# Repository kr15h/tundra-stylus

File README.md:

# Tundra Stylus

> This project has migrated. See [Lighthouse Stylus](https://gitlab.com/kriwkrow/lighthouse-stylus).

Tundra Tracker stylus baseplate for 3D positional tracking. This repository contains design files and test application source code. It currently works with [SteamVR](https://store.steampowered.com/app/250820/SteamVR/), but [libsurvive](https://github.com/cntools/libsurvive) support is on its way.

https://github.com/user-attachments/assets/fd64adfa-e3c0-4b6a-a956-ca7f262a2909

## Introduction

Vive Lighthouse system is great! The main use of it is VR, but what about drawing or painting in space? Stylus input is the natural choice of many, but there is no VIVE Lighthouse Stylus available. Logitech almost launched VR Ink, but then decided not to. What to do?

[Tundra Tracker](https://tundra-labs.com/products/additional-tracker) is the smallest available off-the-shelve tracker that is compatible with the VIVE Lighthouse system. It offers a great deal of flexibility via its [IO Expansion Board](https://tundra-labs.com/products/tundra-tracker-io-expansion-board). With that in mind, all we need is a neat circuit board with buttons and a 3D-printable structure that looks and feels like a stylus. 

And that is Tundra Stylus! Produce the circuit board, 3D print the enclosure and you are ready to go, given that you have the Tundra Tracker and its IO Expansion board.

## Getting Started

Here is a table of contents of different documentation sections that will tell you what to do. You can also jump right to the design, electronics and software sections if you know all that by heart and prefer not to read too much documentation. It is up to you.

- [BOM](docs/BOM.md)  
  Start here as you will need to purchase some things to get started.
- [PCB Production](docs/PCB_PRODUCTION.md)  
  This may take time too so better start early.
- [3D Printing](docs/3D_PRINTING.md)  
  This one is relatively fast, given you have FDM printer available.
- [Assembly](docs/ASSEMBLY.md)  
  Putting it all together should be not hard, given you have all the parts (and tools).
- [Usage](docs/USAGE.md)  
  The setup and software part of the process.
- [Contributing](docs/CONTRIBUTING.md)  
  You are willing to improve something? Great!

## License

This repository contains multiple components, each licensed under different terms. Please review the specific license for each component below.

1. The CAD files in this repository are licensed under the **Creative Commons Attribution-NonCommercial 4.0 International (CC BY-NC 4.0)**.
2. The electronics design files in this repository are licensed under the **Creative Commons Attribution-NonCommercial 4.0 International (CC BY-NC 4.0)**.
3. The source code in this repository is licensed under the **MIT License**.

Please consult [LICENSE.md](LICENSE.md) for more detail.

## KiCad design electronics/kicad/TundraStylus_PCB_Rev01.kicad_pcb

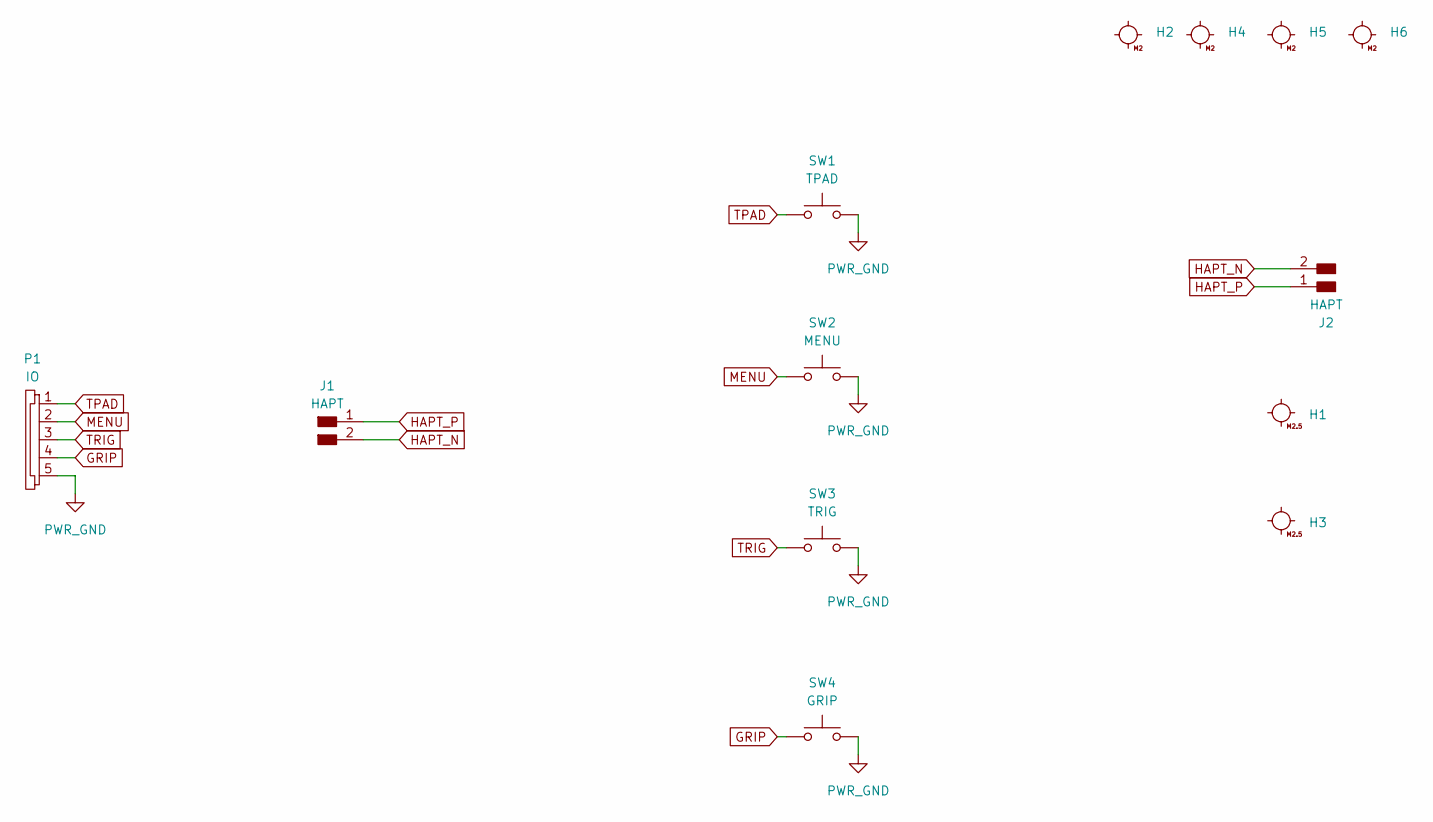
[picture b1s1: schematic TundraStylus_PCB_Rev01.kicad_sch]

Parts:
H1, H3: MountingHole_M2.5
H2, H4, H5, H6: MountingHole_M2
J1, J2: HAPT; Conn_2pos_Plain
P1: IO; Conn_FFC_1x05_P1mm_SideEntry_GCT_FFC3B11-05-T
SW1: TPAD; Button_Omron_B3SN_6.0x6.0mm
SW2: MENU; Button_Omron_B3SN_6.0x6.0mm
SW3: TRIG; Button_Omron_B3SN_6.0x6.0mm
SW4: GRIP; Button_Omron_B3SN_6.0x6.0mm

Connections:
GRIP: P1.4, SW4.1
HAPT_N: J1.2, J2.2
HAPT_P: J1.1, J2.1
MENU: P1.2, SW2.1
PWR_GND: P1.5, SW1.2, SW2.2, SW3.2, SW4.2
TPAD: P1.1, SW1.1
TRIG: P1.3, SW3.1

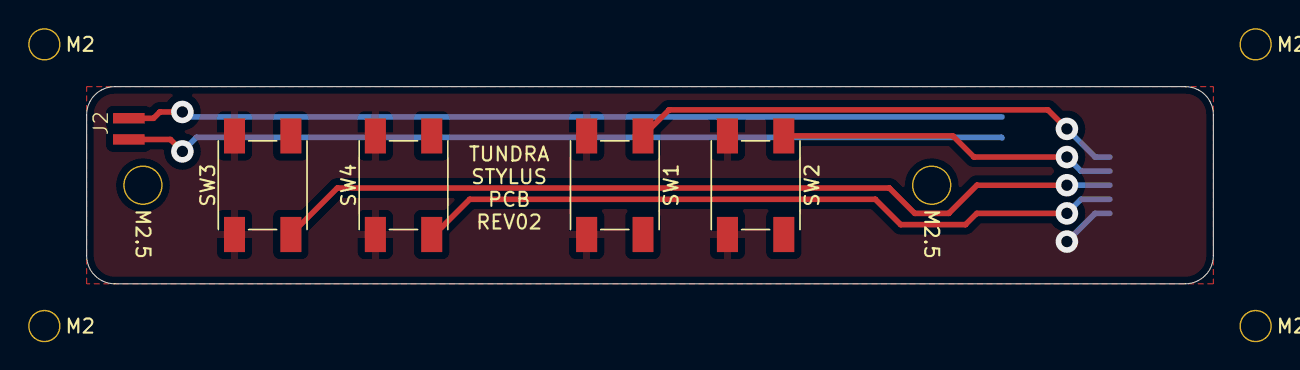
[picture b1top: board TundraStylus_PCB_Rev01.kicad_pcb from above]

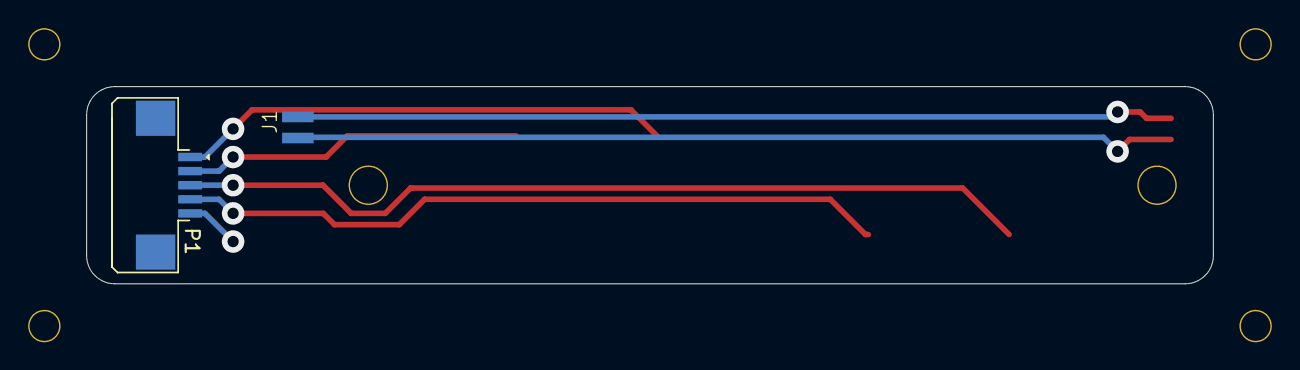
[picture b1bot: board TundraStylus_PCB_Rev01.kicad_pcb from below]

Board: 2 copper layers, 80.0 x 14.0 mm, 13 parts (2 on the bottom side), 7 nets.

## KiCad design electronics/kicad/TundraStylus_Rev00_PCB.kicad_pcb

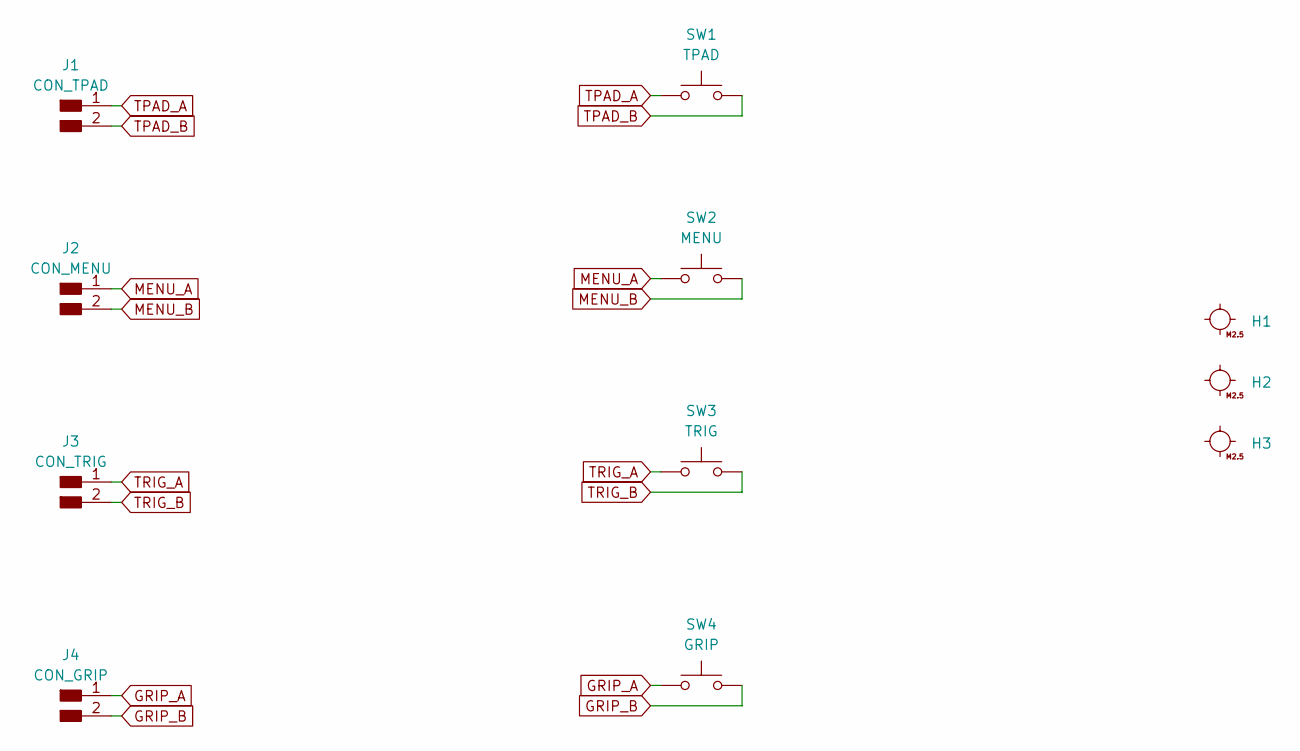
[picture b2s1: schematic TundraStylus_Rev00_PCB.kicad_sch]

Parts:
H1, H2, H3: MountingHole_M2.5
J1: CON_TPAD; PinHeader_1x02_P2.54mm_Horizontal_SMD
J2: CON_MENU; PinHeader_1x02_P2.54mm_Horizontal_SMD
J3: CON_TRIG; PinHeader_1x02_P2.54mm_Horizontal_SMD
J4: CON_GRIP; PinHeader_1x02_P2.54mm_Horizontal_SMD
SW1: TPAD; Button_Omron_B3SN_6.0x6.0mm
SW2: MENU; Button_Omron_B3SN_6.0x6.0mm
SW3: TRIG; Button_Omron_B3SN_6.0x6.0mm
SW4: GRIP; Button_Omron_B3SN_6.0x6.0mm

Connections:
GRIP_A: J4.1, SW4.1
GRIP_B: J4.2, SW4.2
MENU_A: J2.1, SW2.1
MENU_B: J2.2, SW2.2
TPAD_A: J1.1, SW1.1
TPAD_B: J1.2, SW1.2
TRIG_A: J3.1, SW3.1
TRIG_B: J3.2, SW3.2

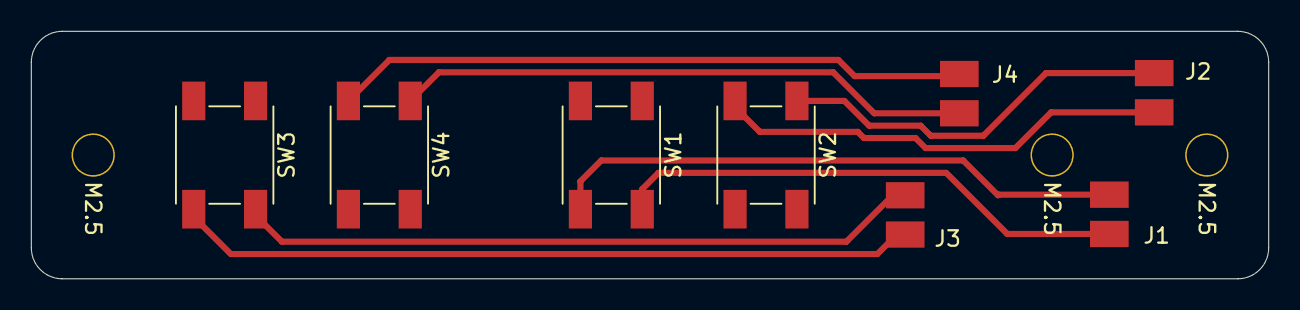
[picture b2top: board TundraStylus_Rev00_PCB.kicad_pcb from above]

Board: 2 copper layers, 80.0 x 16.0 mm, 11 parts (0 on the bottom side), 8 nets.

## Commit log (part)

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2024-12-11 Add first working version
2024-12-14 Add webui until a point where we can test it with steam proxy
2024-12-14 Add other files needed for replication
2024-12-14 Update model rotation
2024-12-14 Map pose matrix to model loaded in threejs scene
2024-12-15 Add websocket connection and realtime status
2024-12-15 Clean up a bit
2024-12-15 Update proxy to send pose only and adjust webui
2024-12-15 Add button state sending to proxy and identify trigger button press and release in webui
2024-12-17 Add StylusManager and implement origin set on MENU button press
2024-12-17 Refactor and set origin based on first stylus added to stylus manager
2024-12-17 Add grid helper
2024-12-17 Show help for setting origin when Set Origin is pressed
2024-12-17 Add multiple stylus capability and simplify scene code
2024-12-17 Add optional verbose mode to proxy
2024-12-17 Refactor a bit more so that the flow is more clear
2024-12-17 Show waiting for stylus until stylus sends first message
2024-12-18 Add bare bones ruler tool that prints distance in console
2024-12-18 Add sprite points and line to scene when using ruler tool
2024-12-18 Add visual label that shows distance between two points
2024-12-19 Play with Z-offset of the morel to compensate tracker origin offset
2024-12-19 Update software directory structure
2024-12-19 Add tool manager and refactor a bit
2024-12-19 Simplify intex.html
2024-12-19 Add freehand tool
2024-12-19 Add clear functionality
2024-12-19 Limit framerate to 30 fps for now, performs better on my little computer
2024-12-19 Set proxy and webui to 60 fps and make the tip shadow smaller
2024-12-26 Add media to root README
2024-12-26 Add gif link to video
2024-12-26 Update gif
2024-12-26 Move images around
2024-12-26 Update gif and add open stylus image
2024-12-26 Update BOM
2024-12-26 Bring tools up in BOM
2024-12-26 Rename Other Parts to just Parts as they are essential parts
2024-12-26 Update root README
2024-12-26 We need 4 bolts and nuts not just 3
2024-12-26 Rename Replicating to Getting Started as we are getting started there
2024-12-27 Update PCB production README
2024-12-27 Add unsaved changes to PCB production README
2024-12-27 Add 3D printing info to docs/3D_PRINTING.md
2024-12-27 Add detail to docs/3D_PRINTING.md
2024-12-27 Populate docs/ASSEMBLY.md
2024-12-27 Populate docs/USAGE.md
2024-12-27 Remove gifs for a moment
2024-12-27 Add progressive loading gifs back
2024-12-28 Add root license and text about it in main README
2024-12-28 Add docs/CONTRIBUTING.md
2024-12-28 Update SteamVR proxy README
2024-12-28 Update license, format MIT license text
2024-12-28 Add PCB manufacturing files for JLCPCB
2024-12-28 Bump version in LICENSE.md
2024-12-29 Update pcb files
2025-01-01 Update before testing
2025-01-01 Make TundraStylus class work as old solution
2025-01-01 Clean up old code from main and TundraStylus
2025-01-01 Clean up some initial zombie code
2025-01-01 Manage stylus waiting modal from outside TundraStylus class
2025-01-01 Clean up old stylus waiting modal code from TundraStylus
2025-01-01 Add TODO.md
2025-01-02 Treat tip position as main position when stylus events come in
2025-01-03 Decouple scene origin from TundraStylus class
2025-01-03 Add custom app instructions to USAGE.md
2025-01-03 Bump version to v0.2.0
2025-01-08 Test mp4 video embed in README.md
2025-01-08 Try full URL for video embed in README.md
2025-01-08 Try with one more trick to embed the video in README.md
2025-01-08 Try another URL for video embed
2025-01-08 Update README.md
    Add video via github assets
2025-01-08 Update USAGE.md
    Replace gifs with videos
2025-01-18 Add photo of PCB from JLCPCB
2025-04-21 Adjust stylus Z offset
2025-04-21 Add new 3D model
2025-04-21 Adjust TundraStylus class and loader to reflect new stylus 3D model
2025-04-21 Fix 3D model
2025-04-21 Add 3D model file with content
2025-10-12 Add latest design adjustments (before 3D printing)
2025-10-12 Add latest electronics design
2025-10-14 Update design tolerances
2025-10-14 Update openvr middleware README, add dependency installation
2025-10-16 Add individual button presssed/released messages
2025-10-21 Handle button presses separate from pose in web app
2025-10-22 fix duplicate button messages
2025-10-22 fix button events not being detected
2025-10-24 Add simple libsurvive test
2025-10-29 Add work-in-progress libsurvive development
2025-10-29 Add missing tolerance to tip design
2025-10-29 Add initial calibrator socket
2026-01-08 Other improvements
2026-02-16 Add calibrator and updated tip design
2026-02-16 Fix duplicate stylus entries coming from middleware
2026-02-16 Add button that opens Projected View in new window
2026-02-16 Add boilerplate for projected view in the form of an index.html and main.js
2026-02-16 Make sure we can open Projected View after closing again
2026-02-16 Show Calibrate button once Projected View is open and bring it to front when Projected View button is pressed again
2026-02-16 Add Calibrate as tool based on ruler, but with more lines, keep it disabled when Projected View is closed
2026-02-16 Notify viewopts when calibration tool has four points collected
2026-02-16 Send calibration points to Projected View window once they are collected
2026-02-16 Draw a quad once calibration data arrive in the Projected View
2026-02-16 Add fullscreen option for Projected View window
2026-02-16 Add .gitignore
2026-02-16 Add marker-based homography flow
2026-02-16 Fix canvas not resizing issue
2026-02-16 Add 4 more steps for full world coordinate homography
2026-02-17 Add warping experiment (too complex)
